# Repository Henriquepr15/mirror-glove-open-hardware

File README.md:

# Mirror Glove Open Hardware

Mirror Glove is an open hardware wearable interface designed for finger motion capture using flexible resistive sensors, an ESP32-C6 Super Mini microcontroller, signal conditioning circuitry, firmware, and a labeled gesture dataset for assistive technology research.

The project was developed as an experimental platform for acquiring analog signals generated by finger flexion. The system uses five flexible sensors positioned on a glove, one for each finger, and converts finger movement into measurable electrical signals. These signals can be used for gesture analysis, motion mirroring, actuator control experiments, and preliminary gesture classification in external computational environments.

## Project goals

* Capture finger motion using five flexible resistive sensors.
* Condition analog signals using voltage dividers and passive RC low-pass filtering.
* Read sensor signals using an ESP32-C6 Super Mini.
* Organize sensor data into a structured gesture dataset.
* Support experimental motion mirroring using a transmitter and receiver architecture.
* Provide open hardware documentation for assistive technology, wearable interfaces, embedded systems, and prosthetics research.

## Repository structure

* `hardware/`: PCB design files, schematics, layout images, Gerber files, and hardware-related documentation.
* `firmware/`: ESP32 firmware for the glove transmitter and receiver/actuator unit.
* `docs/`: build instructions, calibration instructions, testing procedures, and operation notes.
* `bom/`: bill of materials with component specifications and quantities.
* `data/`: raw and processed datasets generated from the Mirror Glove.
* `analysis/`: scripts and notebooks used for signal analysis, PCA, machine learning models, and result generation.
* `figures/`: images, diagrams, plots, confusion matrices, and graphical outputs used in the manuscript.

## Intended audience

This project is intended for undergraduate students, researchers, hardware developers, embedded systems developers, assistive technology researchers, and engineers working with wearable interfaces, gesture capture, rehabilitation engineering, robotics, and experimental prosthetics.

## Skills required

* Soldering and PCB assembly: intermediate to advanced.
* ESP32 firmware development: intermediate.
* KiCad or PCB design review: intermediate.
* Python-based signal analysis: basic to intermediate.
* Wearable prototype assembly: basic to intermediate.

## Hardware overview

The Mirror Glove prototype consists of a wearable glove with five flexible resistive sensors connected to a custom PCB. Each sensor is associated with one finger: thumb, index, middle, ring, and pinky. The analog signal from each sensor is conditioned using a voltage divider and passive RC low-pass filtering before being read by the ESP32 analog inputs.

The hardware was designed to support data acquisition, gesture recording, signal analysis, and future expansion for actuator control or wireless motion mirroring using ESP32-based communication.

## Software overview

The firmware is divided into two main modules:

1. Glove transmitter firmware: reads the five flexible sensors and organizes the sensor values.
2. Receiver/actuator firmware: receives sensor data and can convert proportional finger motion values into actuator commands.

Artificial intelligence and gesture classification are not embedded in the ESP32 firmware in the current version. Machine learning analyses are performed externally using the collected dataset.

## Dataset

The dataset contains labeled samples collected from the Mirror Glove sensors during gesture execution. Each sample includes time information, gesture labels, and the readings from the five flexible sensors. The dataset is intended for signal analysis, exploratory visualization, and preliminary supervised gesture classification.

## Documentation status

This repository is under active organization for submission to the Journal of Open Hardware. Build instructions, calibration procedures, testing instructions, design files, firmware, datasets, and analysis scripts are being organized to support replication and peer review.

## Licenses

Hardware files are intended to be licensed under the CERN Open Hardware Licence Version 2 - Permissive (CERN-OHL-P-2.0).

Software and firmware files are intended to be licensed under the MIT License.

Documentation is intended to be licensed under Creative Commons Attribution 4.0 International (CC-BY 4.0).

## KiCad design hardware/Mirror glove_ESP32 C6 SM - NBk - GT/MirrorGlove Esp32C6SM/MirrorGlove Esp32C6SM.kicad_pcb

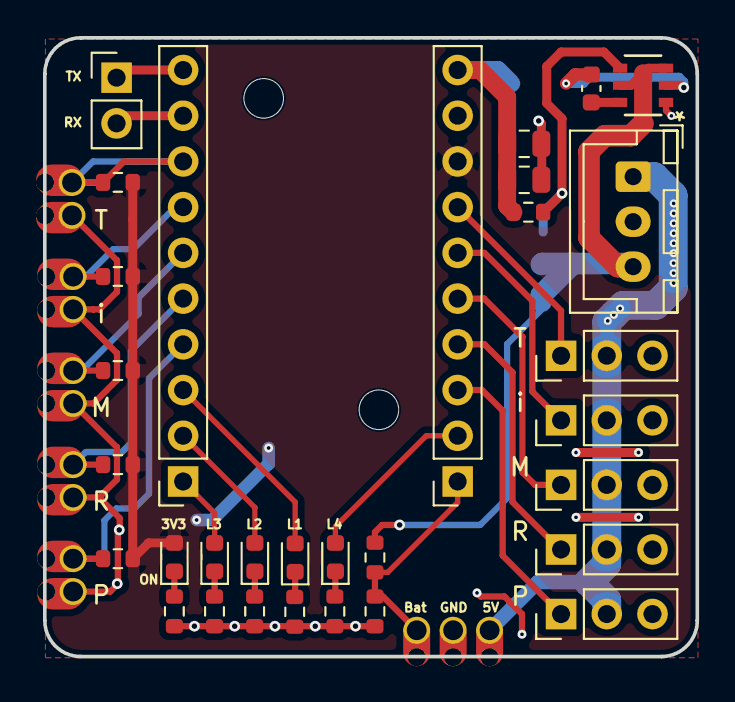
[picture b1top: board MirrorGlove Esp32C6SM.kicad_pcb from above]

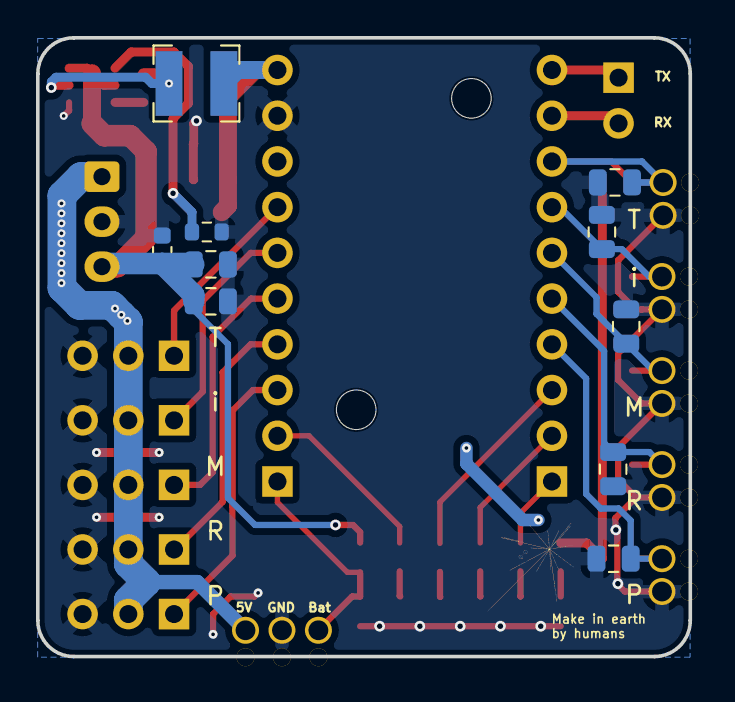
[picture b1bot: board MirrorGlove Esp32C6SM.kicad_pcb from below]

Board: 2 copper layers, 36.2 x 34.4 mm, 51 parts (10 on the bottom side), 30 nets.

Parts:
C1, C2, C3, C4, C5, C14, C20: 10µF; C_0805_2012Metric
C12: 100 nF; C_0603_1608Metric
C13, C18: 4.7; C_0805_2012Metric
C19: 100; C_0603_1608Metric
D2, D4, D5, D6, D7: R; LED_0603_1608Metric
H1, H2: MountingHole; MountingHole_2.2mm_M2_ISO14580
J1, J2: Conn_01x10_Pin; PinSocket_1x10_P2.54mm_Vertical
J4: Conn_01x02_Pin; PinHeader_1x02_P2.54mm_Vertical
J5, J6, J7, J8, J9: Conn_01x02_Socket; BorderTestPoint-2Pad
J10: RING; PinHeader_1x03_P2.54mm_Vertical
J11: PINKY; PinHeader_1x03_P2.54mm_Vertical
J12: THUMB; PinHeader_1x03_P2.54mm_Vertical
J13: INDEX; PinHeader_1x03_P2.54mm_Vertical
J14: MIDDLE; PinHeader_1x03_P2.54mm_Vertical
J15, J16: Conn_01x01_Pin; BorderTestPoint
J17: Conn_01x03_Socket; JST_XH_B3B-XH-A_1x03_P2.50mm_Vertical
L5: 3,3 µH; L_Bourns-SRN4018
R1: 10k; R_0603_1608Metric
R2: 5.1k; R_0603_1608Metric
R5: 1k; R_0603_1608Metric
R7, R8, R9, R10: 300; R_0603_1608Metric
R11, R12, R13, R14, R15: 33k; R_0603_1608Metric
R24: 100k; R_0603_1608Metric
R25: 13.7k; R_0603_1608Metric
TP1: TestPoint; BorderTestPoint
U4: LMR51430YFDDCR; SOT-23-THIN-6_DDC_TEX-L

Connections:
+3.3V: D2.2 (A), J2.8, R11.1, R12.1, R13.1, R14.1, R15.1
+5V_ESP: C14.1, C20.1, J2.10, L5.2, R24.1
+5V_SV: J10.2, J11.2, J12.2, J13.2, J14.2, J15.1, J17.1
+8V: C13.1, C18.1, C19.1, J17.3, R1.1, U4.3 (VIN), U4.5 (EN)
/ADC1_SF_T: C1.1, J1.8, J7.2, R11.2
/ADC2_SF_I: C2.1, J1.7, J8.2, R12.2
/ADC3_SF_M: C5.1, J1.6, J9.2, R13.2
/ADC4_SF_R: C4.1, J1.5, J5.2, R14.2
/ADC5_SF_P: C3.1, J1.4, J6.2, R15.2
/BAT_REF: J2.1, R1.2, R2.1, TP1.1
/LED_1: D7.2 (A), J1.3
/LED_2: D6.2 (A), J1.2
/LED_3: D5.2 (A), J1.1
/LED_4: D4.2 (A), J2.2
/RX: J1.9, J4.2
/SERVO_INDEX: J2.6, J13.1
/SERVO_MIDDLE: J2.5, J14.1
/SERVO_PINKY: J2.3, J11.1
/SERVO_RING: J2.4, J10.1
/SERVO_THUMB: J2.7, J12.1
/TX: J1.10, J4.1
GND: C1.2, C2.2, C3.2, C4.2, C5.2, C13.2, C14.2, C18.2, C19.2, C20.2, J2.9, J5.1, J6.1, J7.1, J8.1, J9.1, J10.3, J11.3, J12.3, J13.3, J14.3, J16.1, J17.2, R2.2, R5.1, R7.1, R8.1, R9.1, R10.1, R25.2, U4.1 (GND)
unnamed: D2.1 (K), R5.2
unnamed: D4.1 (K), R7.2
unnamed: D5.1 (K), R8.2
unnamed: D6.1 (K), R9.2
unnamed: D7.1 (K), R10.2
unnamed: C12.1, U4.6 (CB)
unnamed: R24.2, R25.1, U4.4 (FB)
unnamed: C12.2, L5.1, U4.2 (SW)

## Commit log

2026-06-21 Revise README with comprehensive project details
    Expanded the README to provide detailed project information, goals, repository structure, intended audience, required skills, hardware and software overviews, dataset details, documentation status, a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
2026-06-21 Add build instructions for Mirror Glove prototype
    This document outlines the assembly procedure for the Mirror Glove prototype, including required materials, sensor positioning, wiring, signal conditioning, PCB assembly, firmware upload, testing, an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
2026-06-21 Add bill of materials for prototype components
    Added a bill of materials for the prototype, detailing components, specifications, quantities, and usage notes.
2026-06-21 Add final prototype parts list CSV
2026-06-21 Revise bill of materials to CSV format
    Updated the bill of materials to include CSV formatting and added new components.
2026-06-21 Rename docs/bom/bill_of_materials.csv to bom/bill_of_materials.csv
2026-06-21 Rename docs/bom/final_prototype_parts.csv to bom/final_prototype_parts.csv
2026-06-21 Add calibration procedure for Mirror Glove sensors
    This document outlines the calibration procedure for the Mirror Glove flexible sensors, detailing the purpose, required setup, normalization, servo mapping, recommendations, and limitations.
2026-06-21 Add testing procedure for Mirror Glove prototype
    This document outlines the testing procedure for the Mirror Glove prototype, detailing steps for electrical inspection, power-on tests, individual sensor tests, and more.
2026-06-21 Add KiCad design files for Mirror Glove PCB
    Add editable KiCad project, schematic sheets, PCB layout, and custom footprints for the Mirror Glove ESP32-C6 Super Mini hardware version.
2026-06-22 Add exported schematic PDF
    Add schematic PDF exported from the KiCad project for the Mirror Glove hardware.
2026-06-22 Enhance README with Gerber file details and warnings
    Added detailed information about the Gerber files and PCB design considerations.
2026-06-22 Add hardware reference images
    Add PCB 3D renders, sensor positioning diagram, and early breadboard prototype image for Mirror Glove hardware documentation.
2026-06-22 Rename Sensorized Glove Prototype with Flex Sensors.png to Sensorized Glove Prototype with Flex Sensors
2026-06-22 Rename Sensorized Glove Prototype with Flex Sensors to Sensorized Glove Prototype with Flex Sensors.png
2026-06-22 Rename pcb_3d_top_render.png.png to pcb_3d_top_render.png
2026-06-22 Rename early_prototype_breadboard_glove_1_.jpg to early_prototype_breadboard_glove_1.jpg
2026-06-22 Rename early_prototype_breadboard_glove_2_.jpg to early_prototype_breadboard_glove_2.jpg
2026-06-22 Rename early_prototype_breadboard_glove_2.jpg to early_prototype_breadboard_glove_2_.jpg
